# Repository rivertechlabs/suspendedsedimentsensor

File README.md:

# :ocean:Ötz-T: suspended sediment sensor

## A note on versions:

**This sensor is prototype 3.0 (or "version Ötz-T"). The previous prototype 2.0 (or "first version") is found in this [repo](https://github.com/rivertechlabs/turbiditysensor) (new repo because I consider the two versions different enough).**

## News!

**This sensor was published in HardwareX! Read [Ötz-T: 3D-printed open-source turbidity sensor with Arduino shield for suspended sediment monitoring](https://linkinghub.elsevier.com/retrieve/pii/S2468067223000020).**

-----------------------------------------

**Improvements on this version:**
- :sleeping: Low-power [Arduino MRK WAN 1310](https://store-usa.arduino.cc/products/arduino-mkr-wan-1310) microcontroller
- :stuck_out_tongue_winking_eye: Entirely 3D printed design, so no need to beg a technician for help
- :racehorse: Longer battery life
- :dash: Turbidity, temperature and pressure sensor
- :recycle: Programmed with Arduino IDE
- :dancers: Custom printed circuit board (PCB) as an Arduino shield for an easier and cleaner assembly with a more durable design 

-----------------------------------------
A 3D-printed, open-source suspended sediment sensor for river network monitoring.
## Introduction
This repo is dedicated to the open-source turbidity sensor. More info can be found here:
- https://rivertechlabs.org/
- https://hyd.ifu.ethz.ch/research/riparian/susp-sed-sense.html

This repo contains several items to build the current prototype of the open-source turbidity sensor including:
- The code needed to upload to the microcontroller
- 3D printing files
- PCB files
- CAD files

## Code
There are two codes in the Code folder: main.ino and set_time.ino. Please follow the instructions in set time.ino about changing the date in the program. After the program has flashed, every time the Arduino restarts (disconnect and reconnect to power) it will restart the RTC time to the original compile time of the set time.ino program. To mitigate this issue, the next program, main.ino, can be immediately flashed without disconnecting power or set time.ino can be re-flashed after commenting-out line 79 (“setPCF85263();”). Follow by flashing main.ino onto the Arduino. Please note that additional libraries may need to be downloaded and added to your library (e.g. the [MS5803-05 external library](https://github.com/millerlp/MS5803_05)). The main.ino program was written to take a measurement every hour (one measurement is an average of 15 measurements) to conserve battery, but this can be changed in the code if you require higher temporal resolution to capture larger variability e.g. from flushing of sediment from a dam.

## 3D printing files
Here you will find the printer files (.gcode) and the PrusaSlicer files (.3mf). The CAD files were exported as .stp and imported into the PrusaSlicer program (free). See the .3mf files to understand the settings we used in PrusaSlicer for optimal printing. The main settings were:
- Avoid crossing perimeters [enabled]: so that there was less material to clean after printing
- 5 perimeters, 5 bottom solid layers, and AT LEAST 0.15mm layer height for all components (on the thread and cap to ensure they were waterproof, see this [article](https://blog.prusa3d.com/watertight-3d-printing-pt1-vases-cups-and-other-open-models_48949/))
- The lens inserts ("zapfen") have an even smaller layer height
- The "teeth" have variable layer height (ranging from 0.07-0.15mm to ensure that the zapfen fit into the teeth)

The .3mf files were exported as .gcode files and then printed on a Prusa I3 Mk3 and/or Mk3S Filament Printer.

## PCB
We have provided the Gerber files to directly order the PCBs. Alternatively, the .PcbDoc and .SchDoc files can be opened in Altium (the eductional license can be obtained for free) where you can export your own Gerber files. Finally, the schematic and PCB files were also provided as KiCad files so that they can be viewed and edited without Altium.

## CAD
In this folder we have the original CAD files (as STEP) so that they can be downloaded and adjusted for your project.

## Contact
For questions, please email me at droujko@ifu.baug.ethz.ch or @rivertechjess on Twitter :bird:

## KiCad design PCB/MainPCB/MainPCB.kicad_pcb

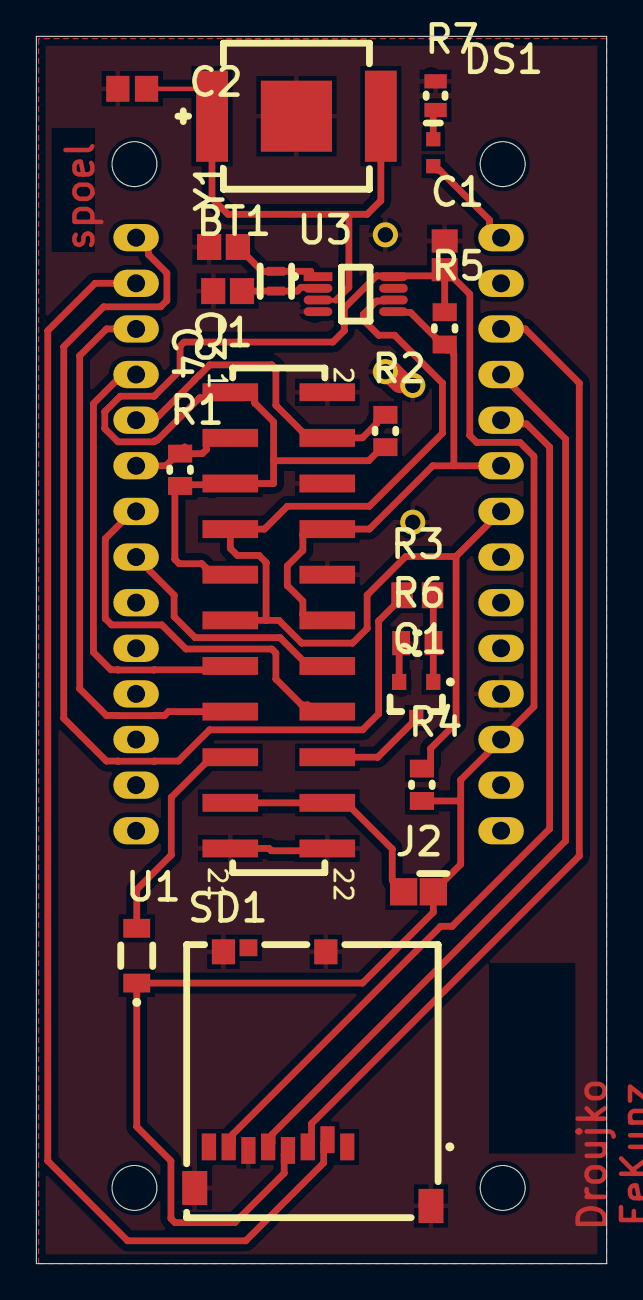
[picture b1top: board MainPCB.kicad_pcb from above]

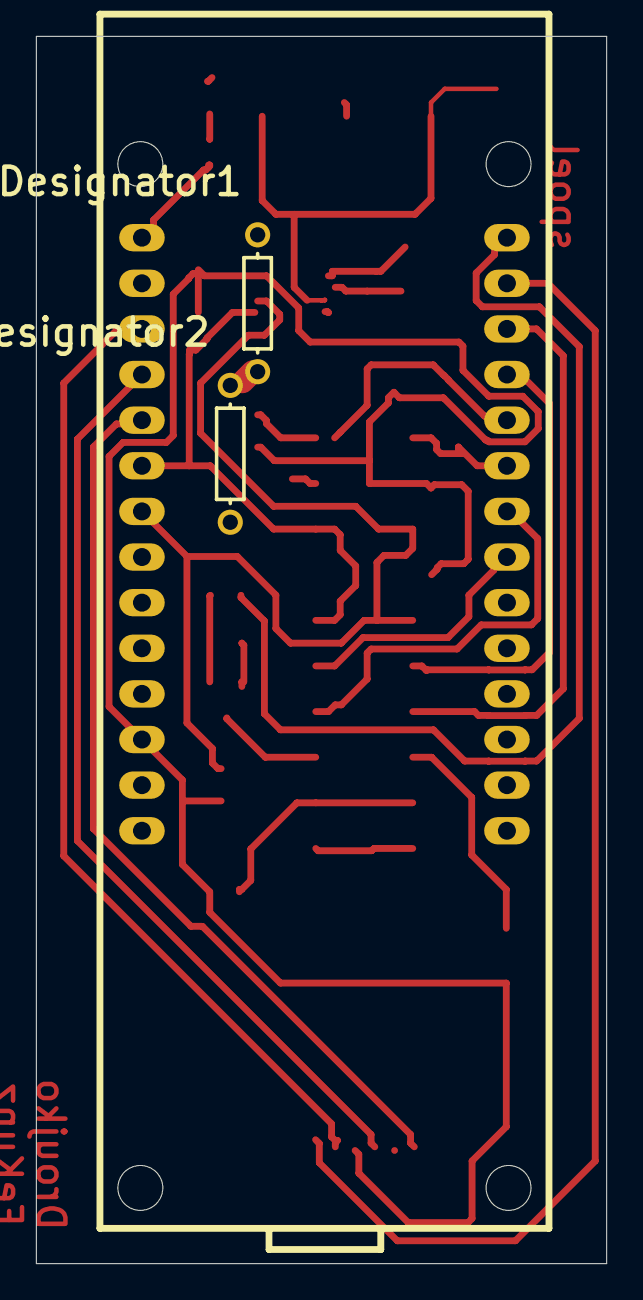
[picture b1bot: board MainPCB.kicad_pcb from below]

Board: 2 copper layers, 31.7 x 68.3 mm, 23 parts (3 on the bottom side), 24 nets.

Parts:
BT1: LR621; FP-2998-MFG
C1, C2: 100nF; CAPC2013X140X50NL20T25
C3, C4: 10pF; CAPC2013X115X51NL20T26
DS1: HSMH-C190; AVAG-HSMX-C190_V
Designator1, Designator2: Comment; _Users_Public_Documents_Altium_AD21_Library_Miscellaneous D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
J1: 61002221121
J2: Jumper_2W; 2w_Jumper
Q1: 2N7002LT1G; ONSC-SOT-23-3-318-08_V
R1, R2, R4, R5: 10k; RESC2013X60X35NL10T20
R3: 330R; RESC2013X60X40NL20T25
R6: n.c.; RESC2013X60X35NL10T20
R7: 330R; RESC2013X60X35LL10T20
SD1: 473521001; MOLX-473521001_V
U1: AL5809-50P1-7; DIOD-POWERDI123-2_B_V
U2: Arduino MKR 1310; ArduinoMKR
U3: PCF85263ATT/AJ; FP-SOT505-1-IPC_B
Y1: 32.768KHZ; FP-ABS05-MFG

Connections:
Anode: J1.17, U1.2
CS: SD1.2, U2.13
DIR: J1.15, U2.12
GND: BT1.1, C1.1, C2.1, C3.1, C4.1, Designator1.1, Designator1.2, Designator2.1, Designator2.2, J1.2, J1.6, J1.10, J1.21, J1.22, Q1.2, R6.1, R7.2, SD1.6, SD1.10, SD1.11, SD1.12, SD1.13, U2.25, U3.4
IR_LED: R3.1, U2.14
Kathode: J1.18, Q1.3
MISO: SD1.7, U2.19
MOSI: SD1.3, U2.17
MOTOR_SUPPLY_EN: J1.14, U2.7
Motor_EN: J1.16, U2.8
NetBT1_2: BT1.2, C2.2, U3.3
NetC3_2: C3.2, U3.1, Y1.1
NetC4_2: C4.2, U3.2, Y1.2
NetDS1_1: DS1.1, U2.15
NetDS1_2: DS1.2, R7.1
NetQ1_1: Q1.1, R3.2, R6.2
SCK_SPI: SD1.5, U2.18
SCL_1: J1.7, J1.11, R4.1, U2.21, U3.6
SCL_2: J1.3, R1.1, U2.9
SDA_1: J1.8, J1.12, R5.1, U2.20, U3.5
SDA_2: J1.4, R2.1, U2.10
STEP: J1.13, U2.11
VBAT_3V7: J1.19, J1.20, J2.2
VCC_3V3: C1.2, J1.1, J1.5, J1.9, J2.1, R1.2, R2.2, R4.2, R5.2, SD1.4, U1.1, U2.26, U3.8

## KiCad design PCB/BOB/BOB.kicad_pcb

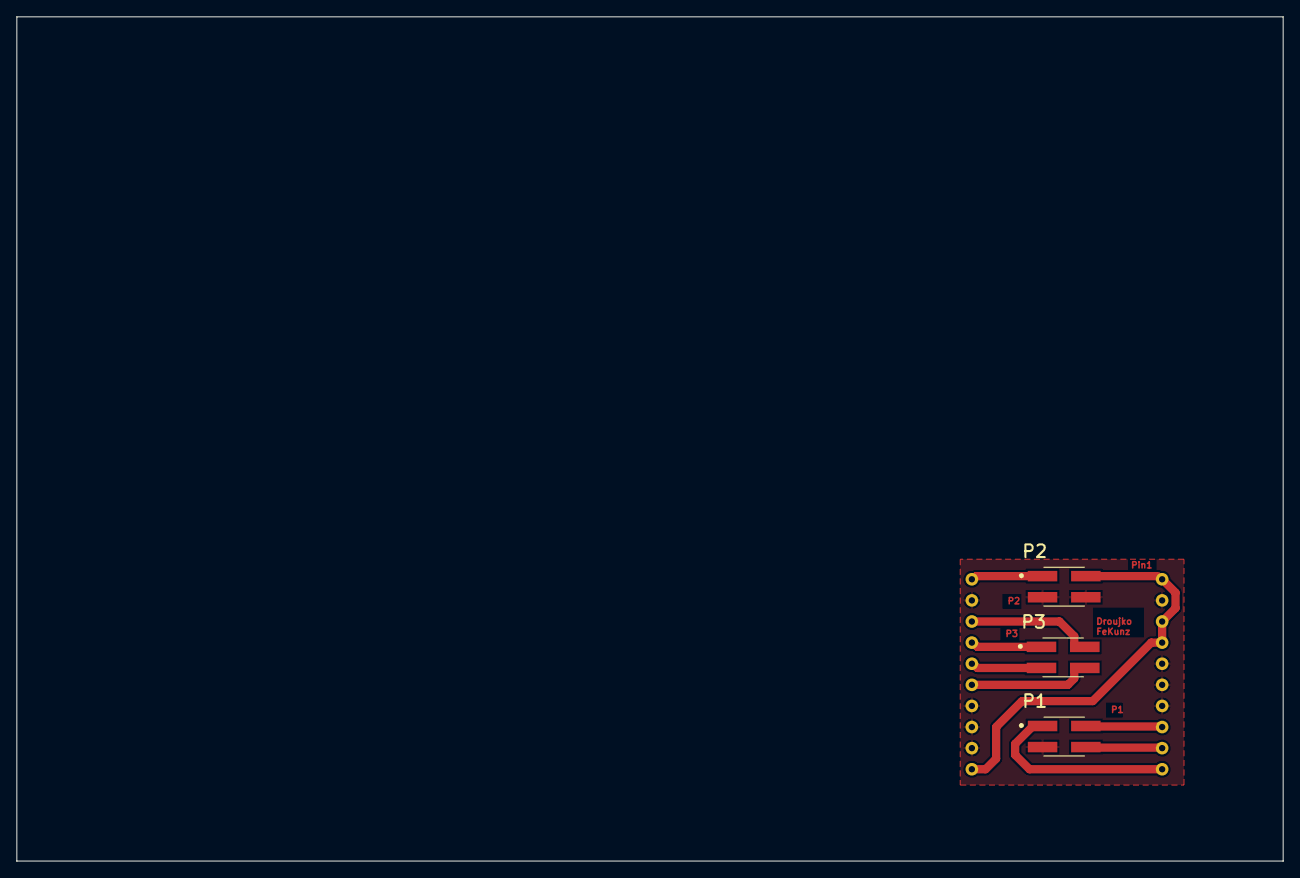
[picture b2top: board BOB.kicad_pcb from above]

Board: 2 copper layers, 152.4 x 101.6 mm, 4 parts (1 on the bottom side), 10 nets.

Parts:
P1, P2, P3: Component_2; Connector
U1: Component_1; BOB

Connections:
DIR: P1.4, U1.9
EN: P1.2, U1.8
GND: P1.3, P2.3, P2.4, U1.2, U1.5, U1.6, U1.7, U1.12, U1.17, U1.18, U1.19
OA1: P3.1, U1.14
OA2: P3.2, U1.13
OB1: P3.3, U1.15
OB2: P3.4, U1.16
STEP: P1.1, U1.10
VBAT: P2.1, U1.11
V_PIN: P2.2, U1.1, U1.3, U1.4, U1.20

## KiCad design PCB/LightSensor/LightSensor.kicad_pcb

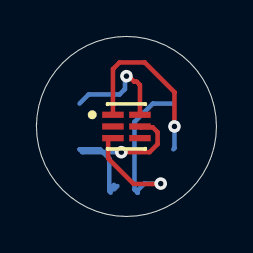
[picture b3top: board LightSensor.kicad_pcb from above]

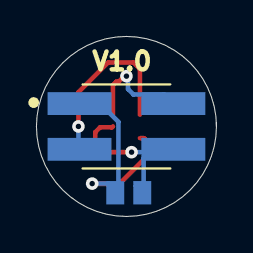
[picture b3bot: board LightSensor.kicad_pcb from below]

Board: 2 copper layers, 10.0 x 10.0 mm, 3 parts (2 on the bottom side), 4 nets.

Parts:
C1: 1uF; CAPC2013X135X45LL10T25
J1: 5-146130-1; TE_5-146130-1
U1: TSL25911FN; AMS-FN-6-2400X2000DE_V

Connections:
GND_PCB_LS: C1.2, J1.1, U1.3
SCL_PCB: J1.3, U1.1
SDA_PCB: J1.2, U1.6
VCC_3V3_PCB_LS: C1.1, J1.4, U1.5

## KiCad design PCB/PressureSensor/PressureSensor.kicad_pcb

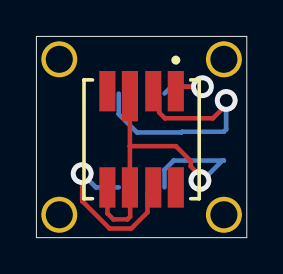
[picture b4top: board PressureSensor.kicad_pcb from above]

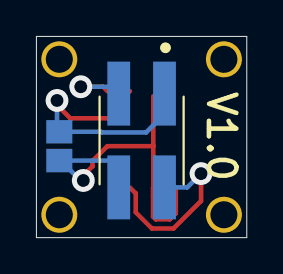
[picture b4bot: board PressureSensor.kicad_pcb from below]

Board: 2 copper layers, 11.7 x 11.2 mm, 3 parts (2 on the bottom side), 4 nets.

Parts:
C1: 100nF; CAPC2013X140X50NL20T25
J1: 5-146130-1; TE_5-146130-1
U1: MS580305BA01-00; FP-MS580301BA01-00-MFG

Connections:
GND_PS_PCB: C1.1, J1.1, U1.2
SCL_1: J1.3, U1.1
SDA_1: J1.2, U1.7
VCC_3V3_PS_PCB: C1.2, J1.4, U1.3, U1.5, U1.6

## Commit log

2022-08-30 PCB Files
